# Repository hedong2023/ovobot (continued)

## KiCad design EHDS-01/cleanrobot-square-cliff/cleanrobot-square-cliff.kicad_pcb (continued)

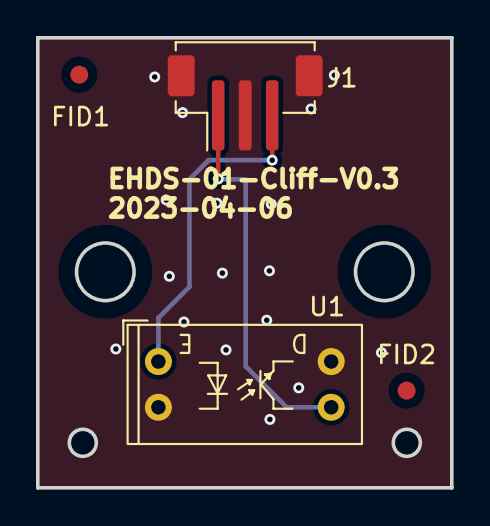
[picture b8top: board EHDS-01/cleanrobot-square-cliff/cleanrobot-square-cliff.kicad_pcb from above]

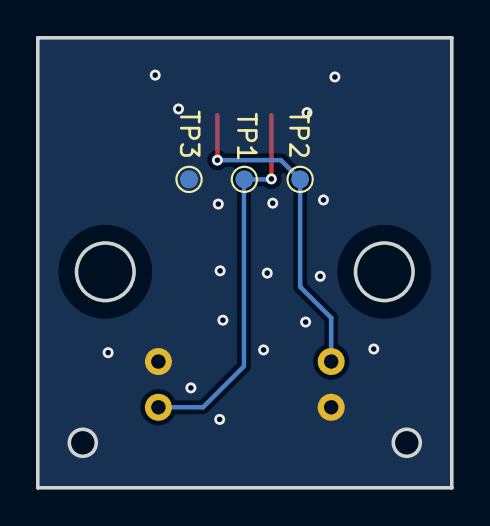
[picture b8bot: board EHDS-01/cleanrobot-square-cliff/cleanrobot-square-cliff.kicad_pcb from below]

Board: 2 copper layers, 23.0 x 25.0 mm, 7 parts (3 on the bottom side), 3 nets.

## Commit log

2024-09-11 添加到git库
2024-09-11 移动烧录位子
2024-09-30 修改封装，修改原理图
